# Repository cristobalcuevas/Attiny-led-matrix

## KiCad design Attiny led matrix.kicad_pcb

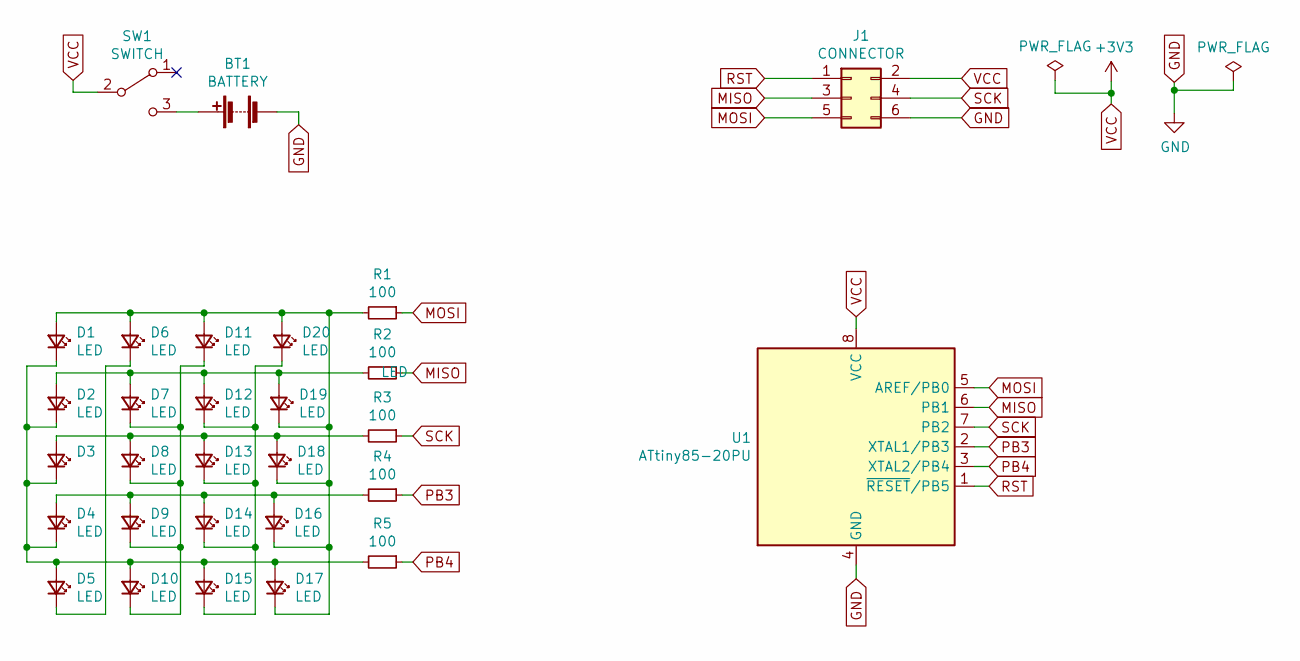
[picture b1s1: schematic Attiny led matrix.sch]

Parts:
BT1: BATTERY; BatteryHolder_Keystone_103_1x20mm
D1, D2, D3, D4, D5, D6, D7, D8, D9, D10, D11, D12, D13, D14, D15, D16, D17, D18, D19, D20: LED; LED_D3.0mm
J1: CONNECTOR; PinHeader_2x03_P2.54mm_Vertical
R1, R2, R3, R4, R5: 100; R_Axial_DIN0204_L3.6mm_D1.6mm_P5.08mm_Horizontal
SW1: SWITCH; SW_CuK_JS202011CQN_DPDT_Straight
U1: ATtiny85-20PU; DIP-8_W7.62mm

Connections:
GND: BT1.2 (-), J1.6, U1.4 (GND)
MISO: J1.3, R2.1, U1.6 (PB1)
MOSI: J1.5, R1.1, U1.5 (AREF/PB0)
unnamed: BT1.1 (+), SW1.3 (C)
unnamed: D1.1 (K), D2.1 (K), D3.1 (K), D4.1 (K), D5.2 (A), D10.2 (A), D15.2 (A), D17.2 (A), R5.2
unnamed: D1.2 (A), D6.2 (A), D11.2 (A), D16.1 (K), D17.1 (K), D18.1 (K), D19.1 (K), D20.2 (A), R1.2
unnamed: D5.1 (K), D6.1 (K)
unnamed: D7.1 (K), D8.1 (K), D9.1 (K), D10.1 (K), D11.1 (K)
unnamed: D12.1 (K), D13.1 (K), D14.1 (K), D15.1 (K), D20.1 (K)
unnamed: D2.2 (A), D7.2 (A), D12.2 (A), D19.2 (A), R2.2
unnamed: D3.2 (A), D8.2 (A), D13.2 (A), D18.2 (A), R3.2
unnamed: D4.2 (A), D9.2 (A), D14.2 (A), D16.2 (A), R4.2
PB3: R4.1, U1.2 (XTAL1/PB3)
PB4: R5.1, U1.3 (XTAL2/PB4)
RST: J1.1, U1.1 (~RESET~/PB5)
SCK: J1.4, R3.1, U1.7 (PB2)
VCC: J1.2, SW1.2 (B), U1.8 (VCC)

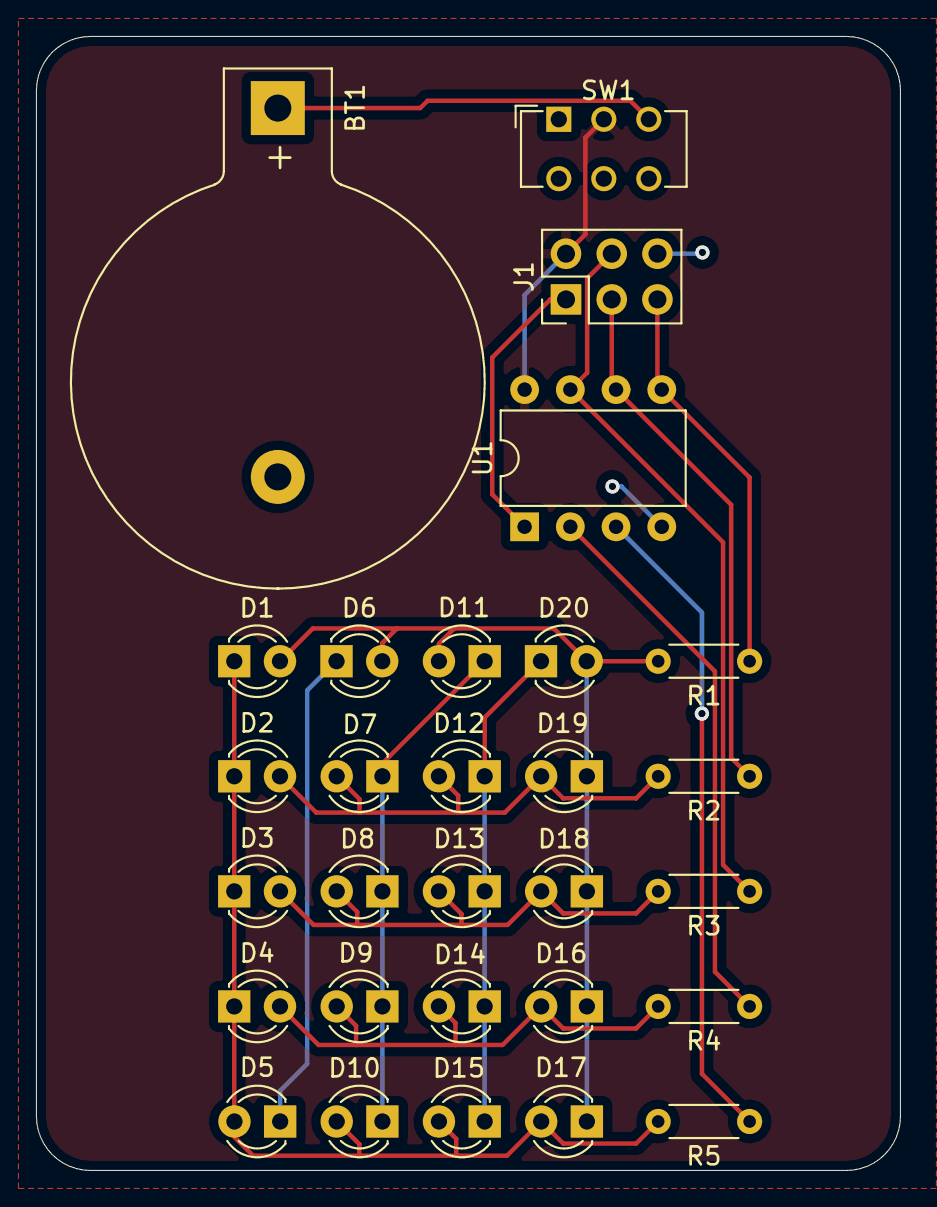
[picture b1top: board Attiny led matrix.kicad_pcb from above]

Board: 2 copper layers, 48.0 x 63.0 mm, 29 parts (0 on the bottom side), 17 nets.
